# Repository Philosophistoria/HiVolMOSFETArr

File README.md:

View this project on [CADLAB.io](https://cadlab.io/project/1984). 

# HiVolMOSFETArr

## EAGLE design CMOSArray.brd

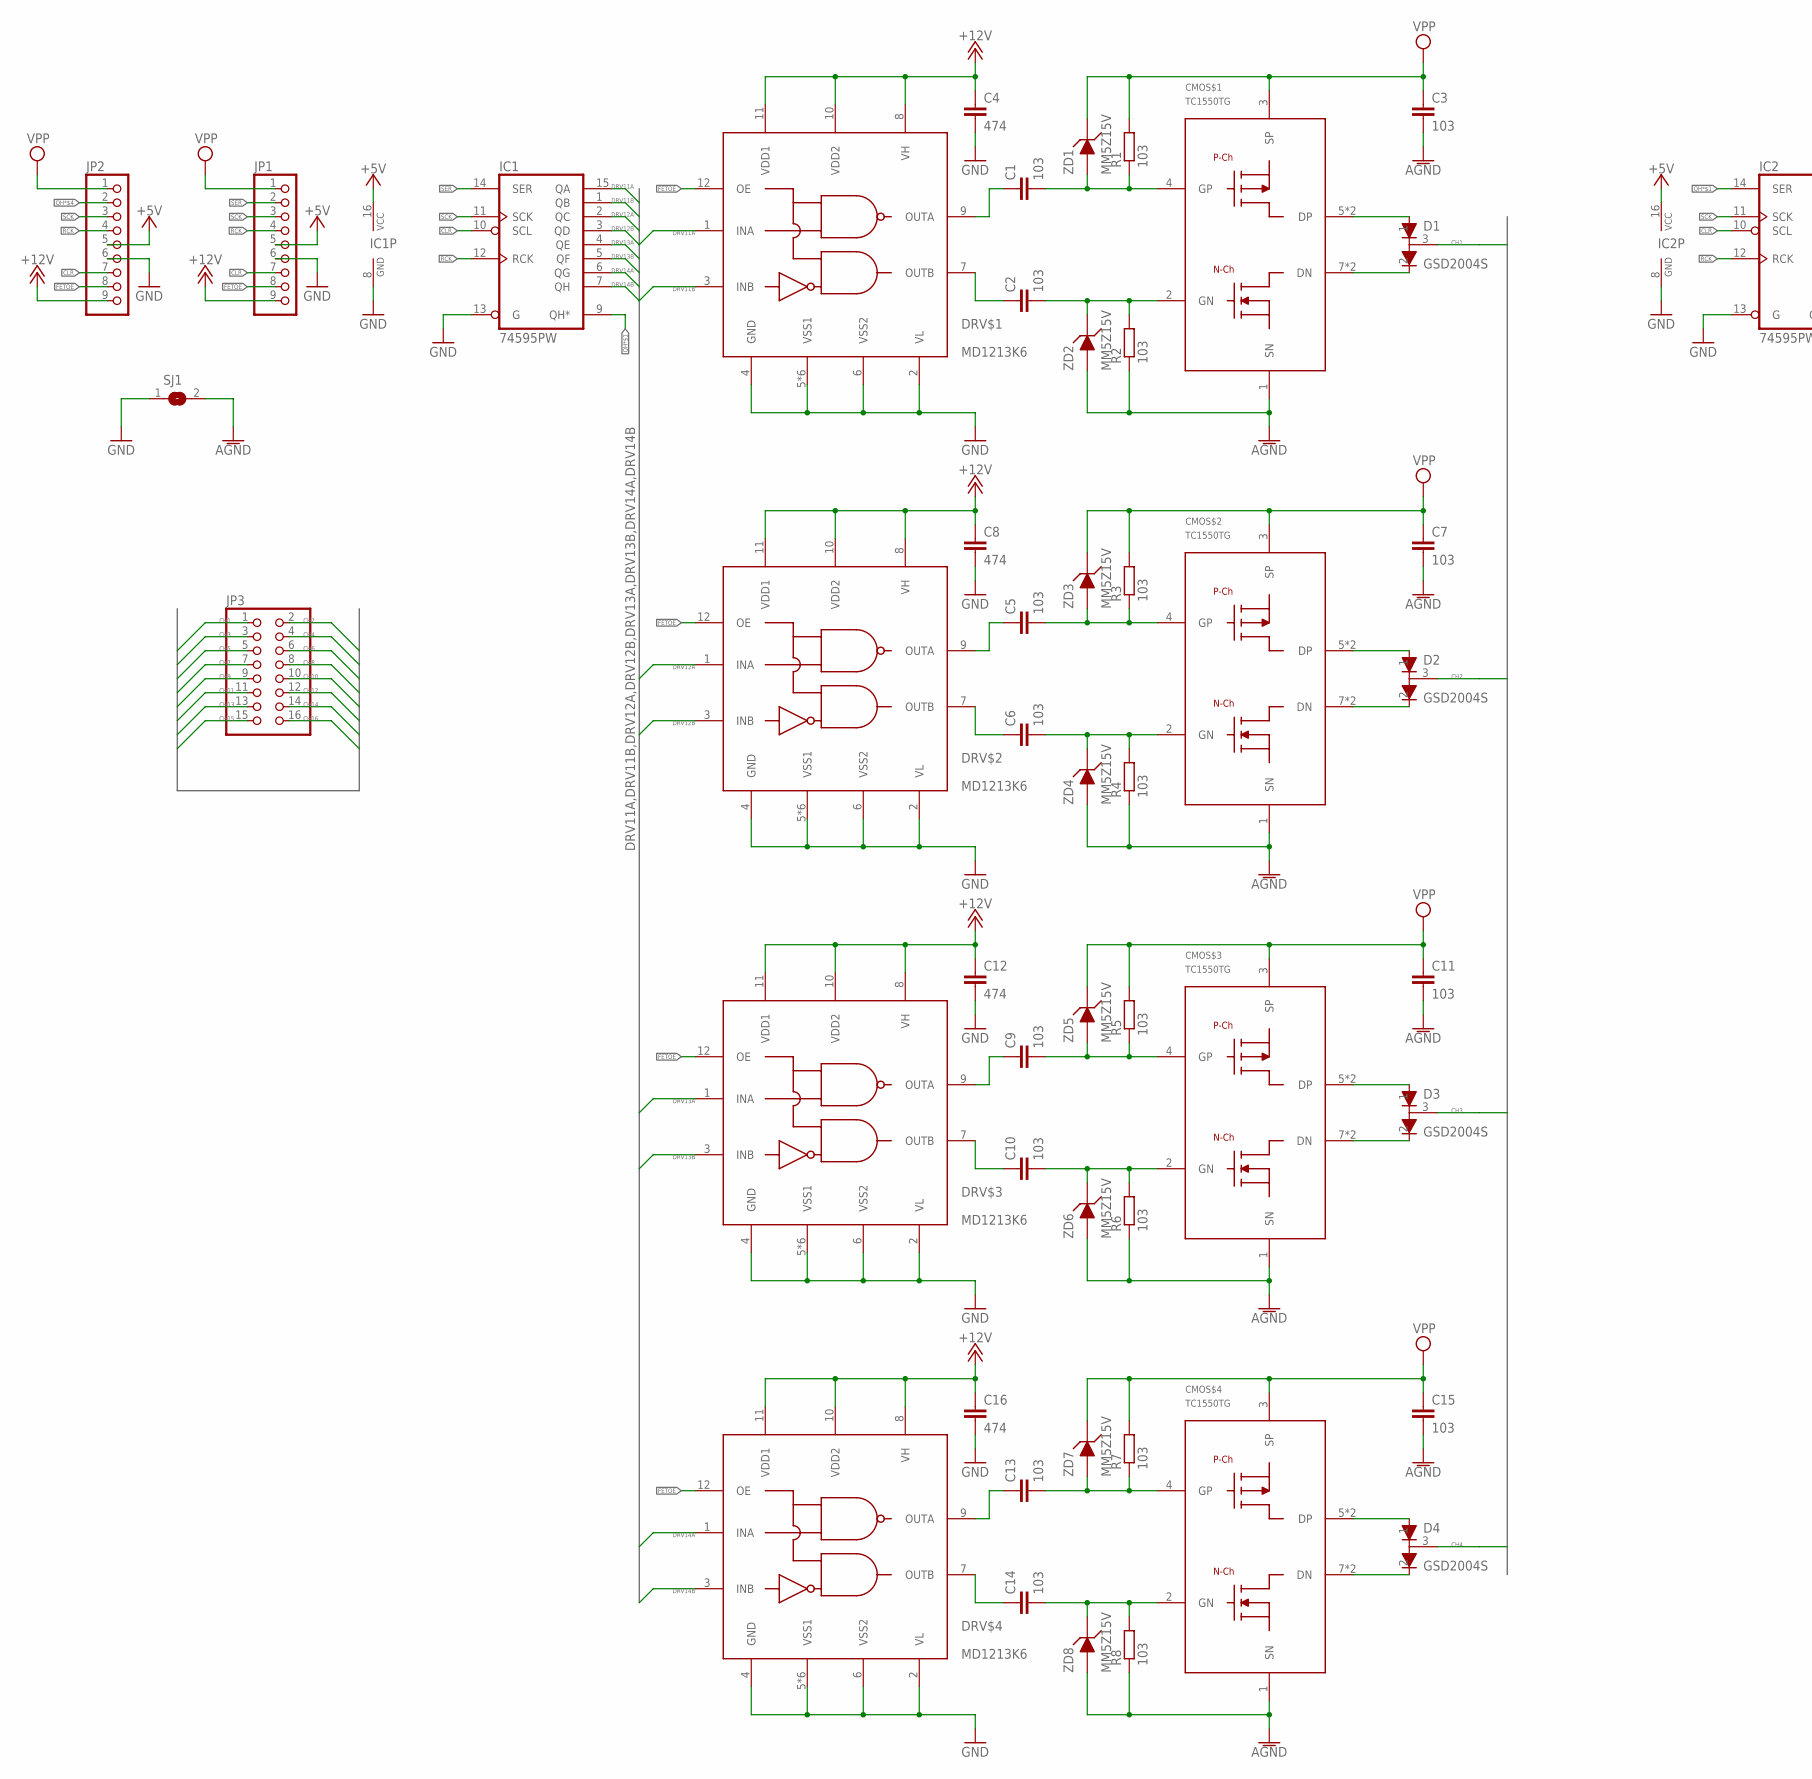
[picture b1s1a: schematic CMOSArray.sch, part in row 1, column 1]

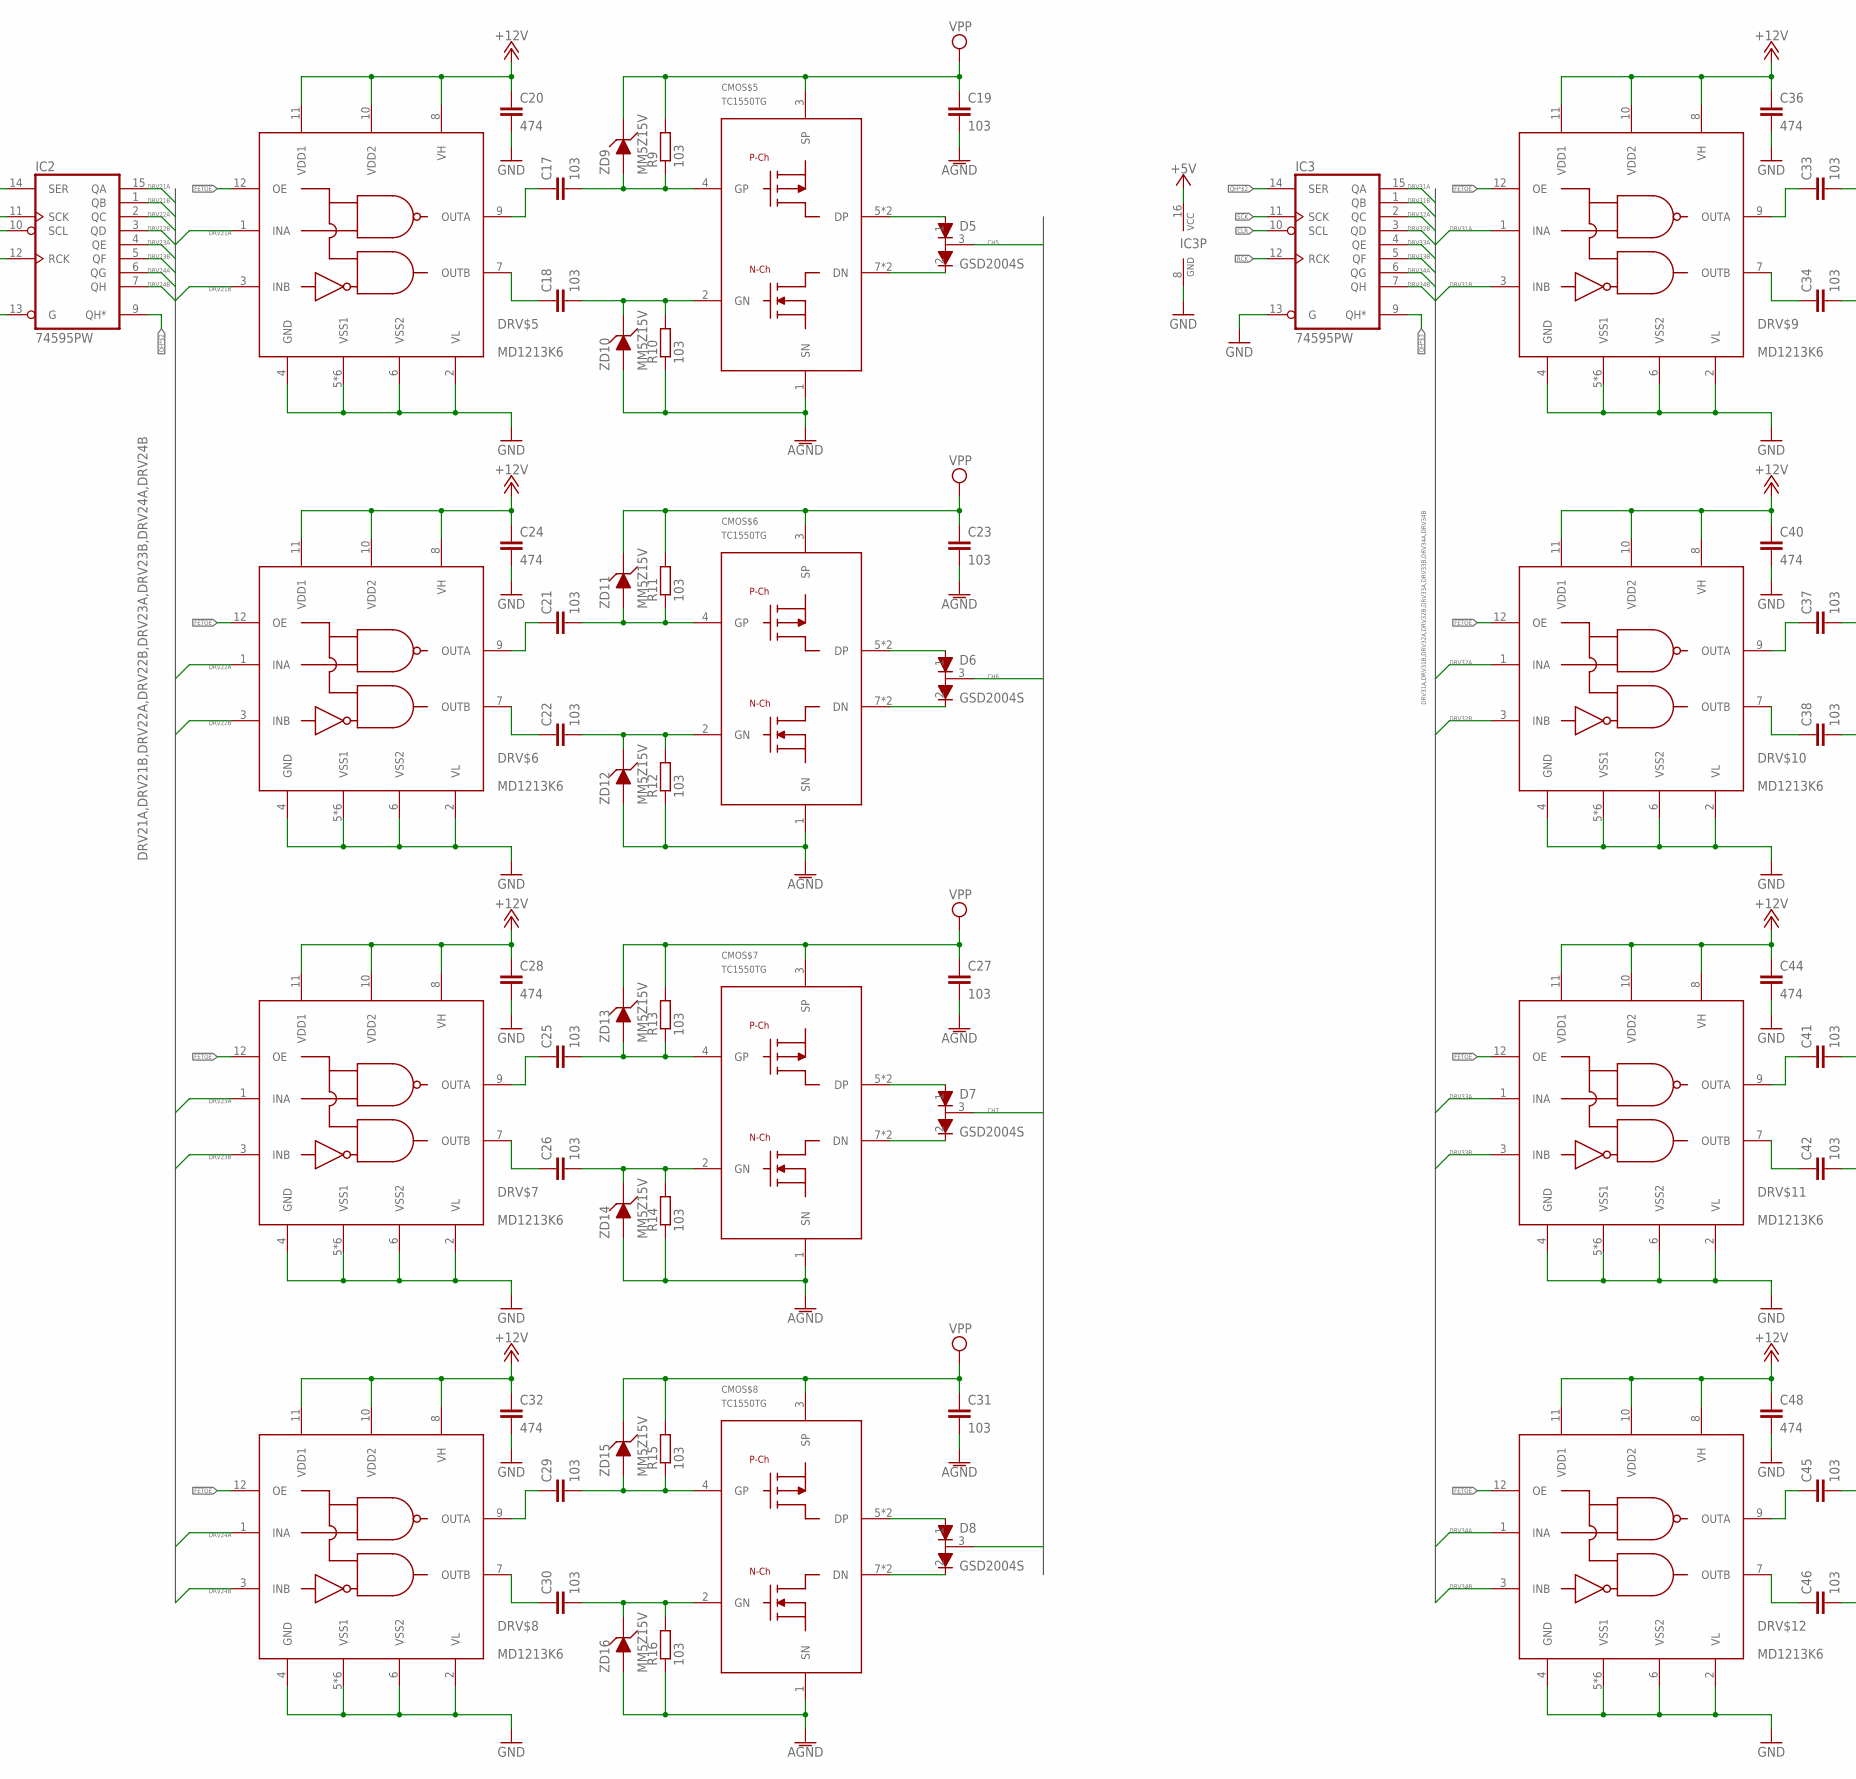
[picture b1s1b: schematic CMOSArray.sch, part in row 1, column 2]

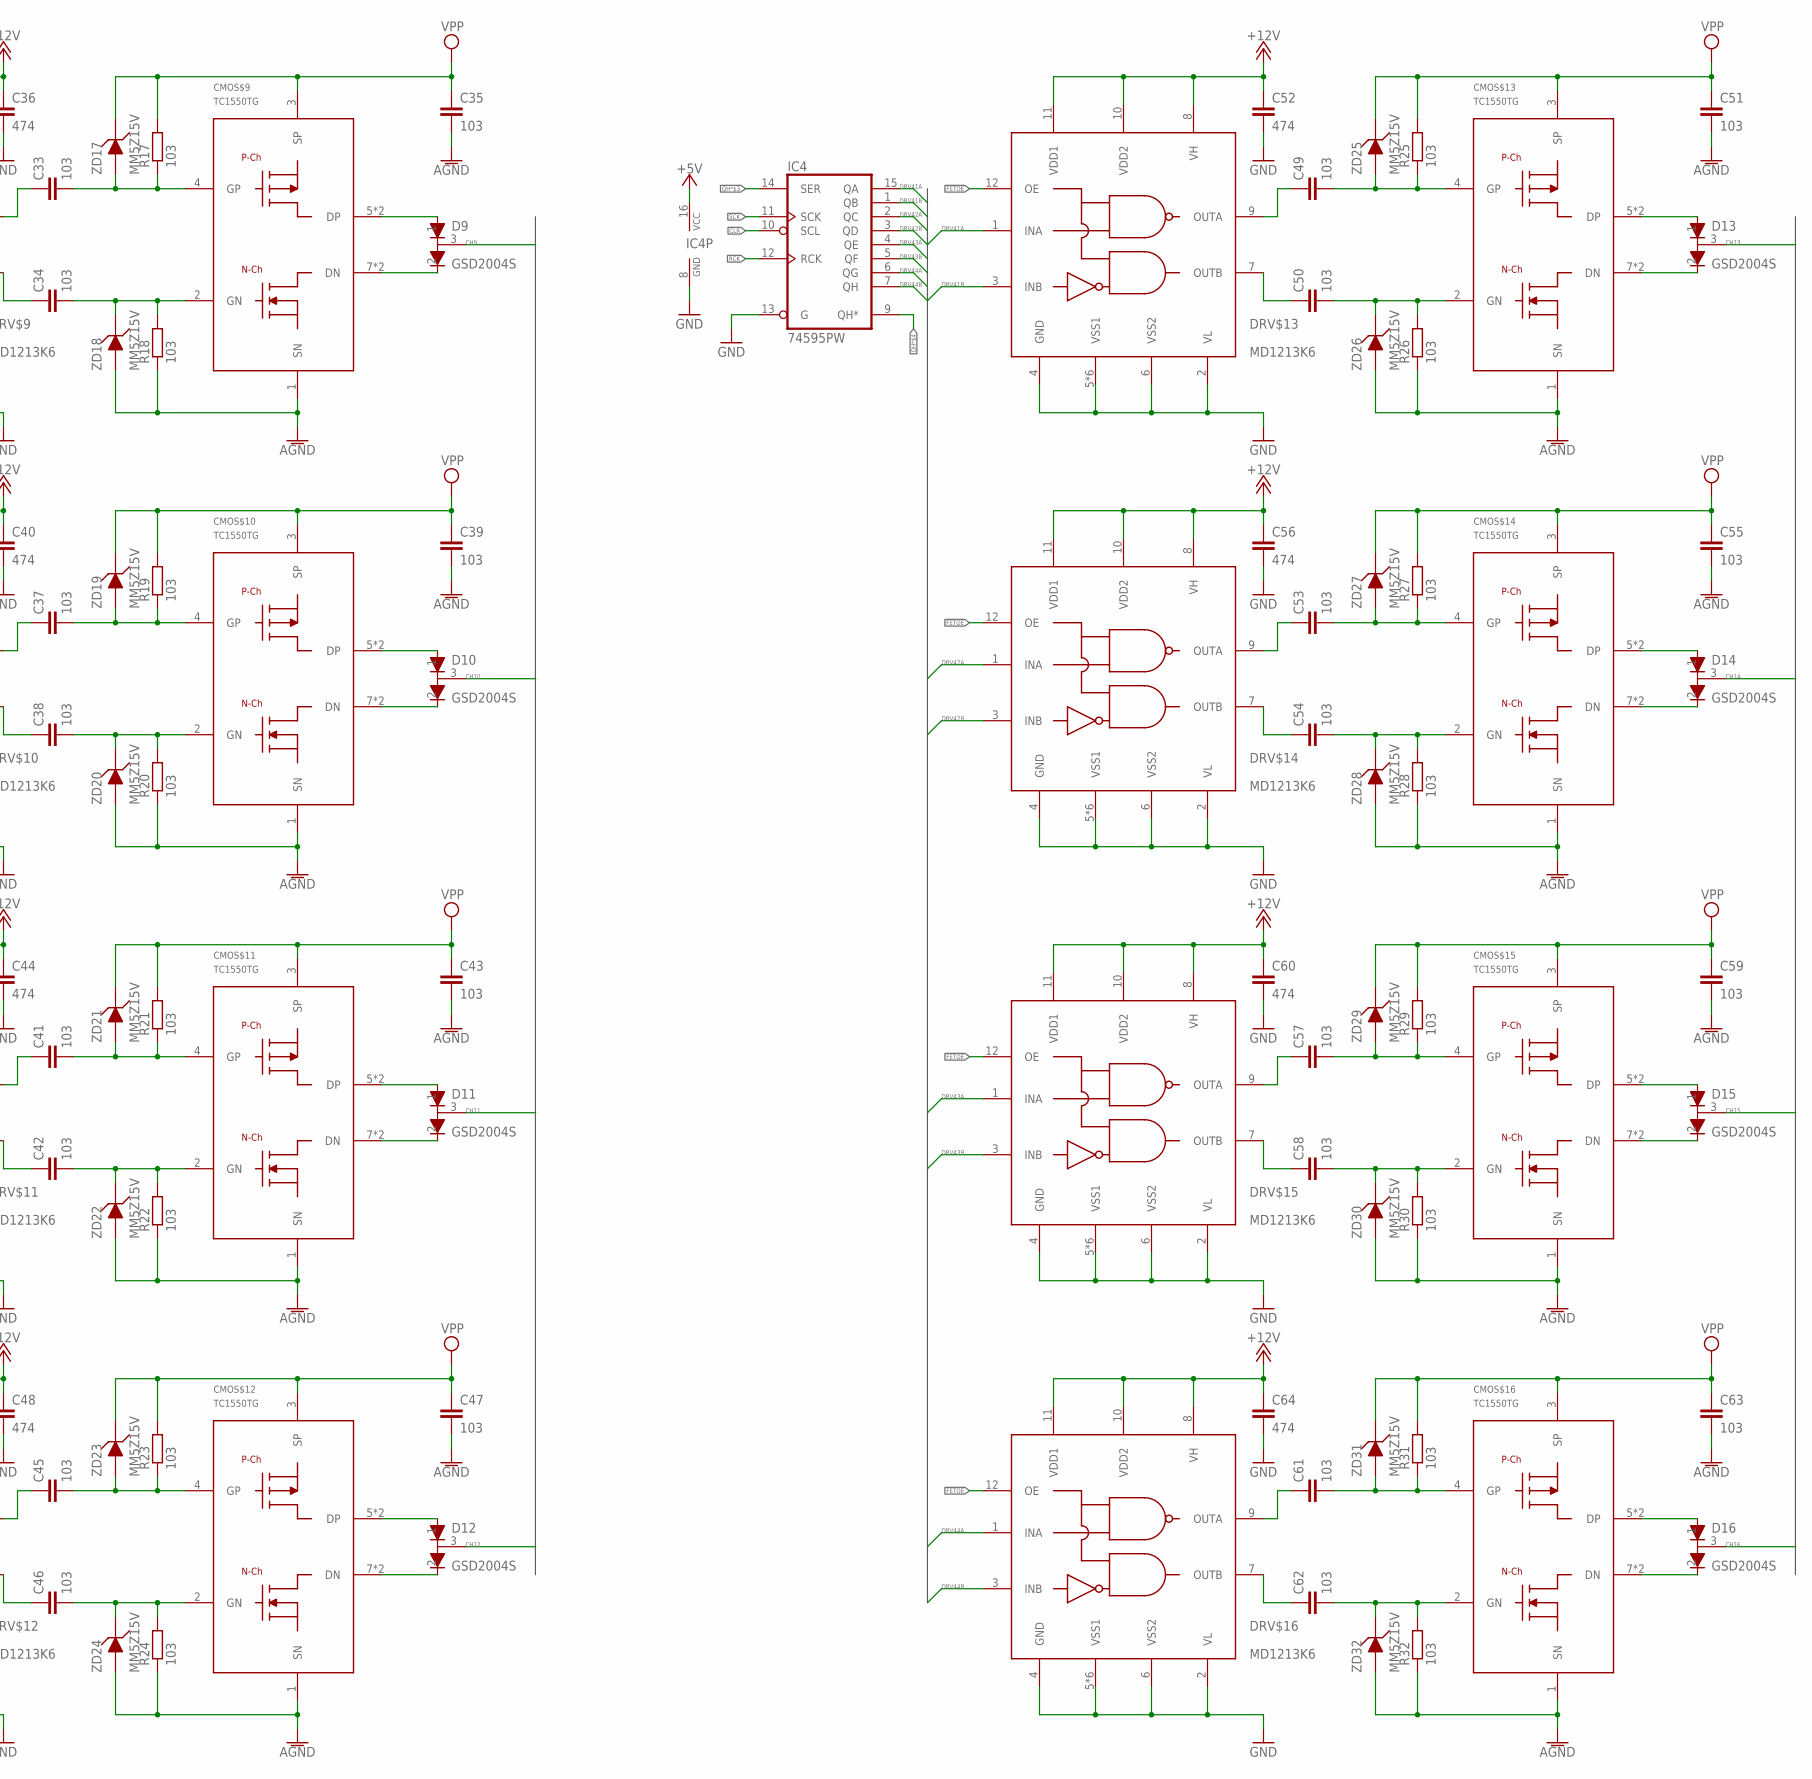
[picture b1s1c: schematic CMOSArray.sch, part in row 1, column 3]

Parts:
C1, C2, C3, C5, C6, C7, C9, C10, C11, C13, C14, C15, C17, C18, C19, C21, C22, C23, C25, C26, C27, C29, C30, C31, C33, C34, C35, C37, C38, C39, C41, C42, C43, C45, C46, C47, C49, C50, C51, C53, C54, C55, C57, C58, C59, C61, C62, C63: 103; C3216
C4, C8, C12, C16, C20, C24, C28, C32, C36, C40, C44, C48, C52, C56, C60, C64: 474; C0402
CMOS$1, CMOS$2, CMOS$3, CMOS$4, CMOS$5, CMOS$6, CMOS$7, CMOS$8, CMOS$9, CMOS$10, CMOS$11, CMOS$12, CMOS$13, CMOS$14, CMOS$15, CMOS$16: TC1550TG; SOIC-08LG
D1, D2, D3, D4, D5, D6, D7, D8, D9, D10, D11, D12, D13, D14, D15, D16: GSD2004S; SOT23
DRV$1, DRV$2, DRV$3, DRV$4, DRV$5, DRV$6, DRV$7, DRV$8, DRV$9, DRV$10, DRV$11, DRV$12, DRV$13, DRV$14, DRV$15, DRV$16: MD1213K6; QFN12
IC1, IC2, IC3, IC4: 74595PW; TTSOP16
JP1, JP2: PINHD-1X9; 1X09
JP3: PINHD-2X8; 2X08
R1, R2, R3, R4, R5, R6, R7, R8, R9, R10, R11, R12, R13, R14, R15, R16, R17, R18, R19, R20, R21, R22, R23, R24, R25, R26, R27, R28, R29, R30, R31, R32: 103; R0402
SJ1: SJ
ZD1, ZD2, ZD3, ZD4, ZD5, ZD6, ZD7, ZD8, ZD9, ZD10, ZD11, ZD12, ZD13, ZD14, ZD15, ZD16, ZD17, ZD18, ZD19, ZD20, ZD21, ZD22, ZD23, ZD24, ZD25, ZD26, ZD27, ZD28, ZD29, ZD30, ZD31, ZD32: MM5Z15V; SOD523

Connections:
+5V: IC1.16 (VCC), IC2.16 (VCC), IC3.16 (VCC), IC4.16 (VCC), JP1.5, JP2.5
+12V: C4.1, C8.1, C12.1, C16.1, C20.1, C24.1, C28.1, C32.1, C36.1, C40.1, C44.1, C48.1, C52.1, C56.1, C60.1, C64.1, DRV$1.8 (VH), DRV$1.10 (VDD2), DRV$1.11 (VDD1), DRV$2.8 (VH), DRV$2.10 (VDD2), DRV$2.11 (VDD1), DRV$3.8 (VH), DRV$3.10 (VDD2), DRV$3.11 (VDD1), DRV$4.8 (VH), DRV$4.10 (VDD2), DRV$4.11 (VDD1), DRV$5.8 (VH), DRV$5.10 (VDD2), DRV$5.11 (VDD1), DRV$6.8 (VH), DRV$6.10 (VDD2), DRV$6.11 (VDD1), DRV$7.8 (VH), DRV$7.10 (VDD2), DRV$7.11 (VDD1), DRV$8.8 (VH), DRV$8.10 (VDD2), DRV$8.11 (VDD1), DRV$9.8 (VH), DRV$9.10 (VDD2), DRV$9.11 (VDD1), DRV$10.8 (VH), DRV$10.10 (VDD2), DRV$10.11 (VDD1), DRV$11.8 (VH), DRV$11.10 (VDD2), DRV$11.11 (VDD1), DRV$12.8 (VH), DRV$12.10 (VDD2), DRV$12.11 (VDD1), DRV$13.8 (VH), DRV$13.10 (VDD2), DRV$13.11 (VDD1), DRV$14.8 (VH), DRV$14.10 (VDD2), DRV$14.11 (VDD1), DRV$15.8 (VH), DRV$15.10 (VDD2), DRV$15.11 (VDD1), DRV$16.8 (VH), DRV$16.10 (VDD2), DRV$16.11 (VDD1), JP1.9, JP2.9
AGND: C3.2, C7.2, C11.2, C15.2, C19.2, C23.2, C27.2, C31.2, C35.2, C39.2, C43.2, C47.2, C51.2, C55.2, C59.2, C63.2, CMOS$1.1 (SN), CMOS$2.1 (SN), CMOS$3.1 (SN), CMOS$4.1 (SN), CMOS$5.1 (SN), CMOS$6.1 (SN), CMOS$7.1 (SN), CMOS$8.1 (SN), CMOS$9.1 (SN), CMOS$10.1 (SN), CMOS$11.1 (SN), CMOS$12.1 (SN), CMOS$13.1 (SN), CMOS$14.1 (SN), CMOS$15.1 (SN), CMOS$16.1 (SN), R2.1, R4.1, R6.1, R8.1, R10.1, R12.1, R14.1, R16.1, R18.1, R20.1, R22.1, R24.1, R26.1, R28.1, R30.1, R32.1, SJ1.2, ZD2.P$2, ZD4.P$2, ZD6.P$2, ZD8.P$2, ZD10.P$2, ZD12.P$2, ZD14.P$2, ZD16.P$2, ZD18.P$2, ZD20.P$2, ZD22.P$2, ZD24.P$2, ZD26.P$2, ZD28.P$2, ZD30.P$2, ZD32.P$2
CH1: D1.3, JP3.1
CH2: D2.3, JP3.2
CH3: D3.3, JP3.3
CH4: D4.3, JP3.4
CH5: D5.3, JP3.5
CH6: D6.3, JP3.6
CH7: D7.3, JP3.7
CH8: D8.3, JP3.8
CH9: D9.3, JP3.9
CH10: D10.3, JP3.10
CH11: D11.3, JP3.11
CH12: D12.3, JP3.12
CH13: D13.3, JP3.13
CH14: D14.3, JP3.14
CH15: D15.3, JP3.15
CH16: D16.3, JP3.16
CLR: IC1.10 (SCL), IC2.10 (SCL), IC3.10 (SCL), IC4.10 (SCL), JP1.7, JP2.7
DRV11A: DRV$1.1 (INA), IC1.15 (QA)
DRV11B: DRV$1.3 (INB), IC1.1 (QB)
DRV12A: DRV$2.1 (INA), IC1.2 (QC)
DRV12B: DRV$2.3 (INB), IC1.3 (QD)
DRV13A: DRV$3.1 (INA), IC1.4 (QE)
DRV13B: DRV$3.3 (INB), IC1.5 (QF)
DRV14A: DRV$4.1 (INA), IC1.6 (QG)
DRV14B: DRV$4.3 (INB), IC1.7 (QH)
DRV21A: DRV$5.1 (INA), IC2.15 (QA)
DRV21B: DRV$5.3 (INB), IC2.1 (QB)
DRV22A: DRV$6.1 (INA), IC2.2 (QC)
DRV22B: DRV$6.3 (INB), IC2.3 (QD)
DRV23A: DRV$7.1 (INA), IC2.4 (QE)
DRV23B: DRV$7.3 (INB), IC2.5 (QF)
DRV24A: DRV$8.1 (INA), IC2.6 (QG)
DRV24B: DRV$8.3 (INB), IC2.7 (QH)
DRV31A: DRV$9.1 (INA), IC3.15 (QA)
DRV31B: DRV$9.3 (INB), IC3.1 (QB)
DRV32A: DRV$10.1 (INA), IC3.2 (QC)
DRV32B: DRV$10.3 (INB), IC3.3 (QD)
DRV33A: DRV$11.1 (INA), IC3.4 (QE)
DRV33B: DRV$11.3 (INB), IC3.5 (QF)
DRV34A: DRV$12.1 (INA), IC3.6 (QG)
DRV34B: DRV$12.3 (INB), IC3.7 (QH)
DRV41A: DRV$13.1 (INA), IC4.15 (QA)
DRV41B: DRV$13.3 (INB), IC4.1 (QB)
DRV42A: DRV$14.1 (INA), IC4.2 (QC)
DRV42B: DRV$14.3 (INB), IC4.3 (QD)
DRV43A: DRV$15.1 (INA), IC4.4 (QE)
DRV43B: DRV$15.3 (INB), IC4.5 (QF)
DRV44A: DRV$16.1 (INA), IC4.6 (QG)
DRV44B: DRV$16.3 (INB), IC4.7 (QH)
FETOE: DRV$1.12 (OE), DRV$2.12 (OE), DRV$3.12 (OE), DRV$4.12 (OE), DRV$5.12 (OE), DRV$6.12 (OE), DRV$7.12 (OE), DRV$8.12 (OE), DRV$9.12 (OE), DRV$10.12 (OE), DRV$11.12 (OE), DRV$12.12 (OE), DRV$13.12 (OE), DRV$14.12 (OE), DRV$15.12 (OE), DRV$16.12 (OE), JP1.8, JP2.8
GND: C4.2, C8.2, C12.2, C16.2, C20.2, C24.2, C28.2, C32.2, C36.2, C40.2, C44.2, C48.2, C52.2, C56.2, C60.2, C64.2, DRV$1.2 (VL), DRV$1.4 (GND), DRV$1.5 (VSS1), DRV$1.6 (VSS2), DRV$1.THP (VSS1), DRV$1.THV$1 (VSS1), DRV$1.THV$2 (VSS1), DRV$1.THV$3 (VSS1), DRV$1.THV$4 (VSS1), DRV$2.2 (VL), DRV$2.4 (GND), DRV$2.5 (VSS1), DRV$2.6 (VSS2), DRV$2.THP (VSS1), DRV$2.THV$1 (VSS1), DRV$2.THV$2 (VSS1), DRV$2.THV$3 (VSS1), DRV$2.THV$4 (VSS1), DRV$3.2 (VL), DRV$3.4 (GND), DRV$3.5 (VSS1), DRV$3.6 (VSS2), DRV$3.THP (VSS1), DRV$3.THV$1 (VSS1), DRV$3.THV$2 (VSS1), DRV$3.THV$3 (VSS1), DRV$3.THV$4 (VSS1), DRV$4.2 (VL), DRV$4.4 (GND), DRV$4.5 (VSS1), DRV$4.6 (VSS2), DRV$4.THP (VSS1), DRV$4.THV$1 (VSS1), DRV$4.THV$2 (VSS1), DRV$4.THV$3 (VSS1), DRV$4.THV$4 (VSS1), DRV$5.2 (VL), DRV$5.4 (GND), DRV$5.5 (VSS1), DRV$5.6 (VSS2), DRV$5.THP (VSS1), DRV$5.THV$1 (VSS1), DRV$5.THV$2 (VSS1), DRV$5.THV$3 (VSS1), DRV$5.THV$4 (VSS1), DRV$6.2 (VL), DRV$6.4 (GND), DRV$6.5 (VSS1), DRV$6.6 (VSS2), DRV$6.THP (VSS1), DRV$6.THV$1 (VSS1), DRV$6.THV$2 (VSS1), DRV$6.THV$3 (VSS1), DRV$6.THV$4 (VSS1), DRV$7.2 (VL), DRV$7.4 (GND), DRV$7.5 (VSS1), DRV$7.6 (VSS2), DRV$7.THP (VSS1), DRV$7.THV$1 (VSS1), DRV$7.THV$2 (VSS1), DRV$7.THV$3 (VSS1), DRV$7.THV$4 (VSS1), DRV$8.2 (VL), DRV$8.4 (GND), DRV$8.5 (VSS1), DRV$8.6 (VSS2), DRV$8.THP (VSS1), DRV$8.THV$1 (VSS1), DRV$8.THV$2 (VSS1), DRV$8.THV$3 (VSS1), DRV$8.THV$4 (VSS1), DRV$9.2 (VL), DRV$9.4 (GND), DRV$9.5 (VSS1), DRV$9.6 (VSS2), DRV$9.THP (VSS1), DRV$9.THV$1 (VSS1), DRV$9.THV$2 (VSS1), DRV$9.THV$3 (VSS1), DRV$9.THV$4 (VSS1), DRV$10.2 (VL), DRV$10.4 (GND), DRV$10.5 (VSS1), DRV$10.6 (VSS2), DRV$10.THP (VSS1), DRV$10.THV$1 (VSS1), DRV$10.THV$2 (VSS1), DRV$10.THV$3 (VSS1), DRV$10.THV$4 (VSS1), DRV$11.2 (VL), DRV$11.4 (GND), DRV$11.5 (VSS1), DRV$11.6 (VSS2), DRV$11.THP (VSS1), DRV$11.THV$1 (VSS1), DRV$11.THV$2 (VSS1), DRV$11.THV$3 (VSS1), DRV$11.THV$4 (VSS1), DRV$12.2 (VL), DRV$12.4 (GND), DRV$12.5 (VSS1), DRV$12.6 (VSS2), DRV$12.THP (VSS1), DRV$12.THV$1 (VSS1), DRV$12.THV$2 (VSS1), DRV$12.THV$3 (VSS1), DRV$12.THV$4 (VSS1), DRV$13.2 (VL), DRV$13.4 (GND), DRV$13.5 (VSS1), DRV$13.6 (VSS2), DRV$13.THP (VSS1), DRV$13.THV$1 (VSS1), DRV$13.THV$2 (VSS1), DRV$13.THV$3 (VSS1), DRV$13.THV$4 (VSS1), DRV$14.2 (VL), DRV$14.4 (GND), DRV$14.5 (VSS1), DRV$14.6 (VSS2), DRV$14.THP (VSS1), DRV$14.THV$1 (VSS1), DRV$14.THV$2 (VSS1), DRV$14.THV$3 (VSS1), DRV$14.THV$4 (VSS1), DRV$15.2 (VL), DRV$15.4 (GND), DRV$15.5 (VSS1), DRV$15.6 (VSS2), DRV$15.THP (VSS1), DRV$15.THV$1 (VSS1), DRV$15.THV$2 (VSS1), DRV$15.THV$3 (VSS1), DRV$15.THV$4 (VSS1), DRV$16.2 (VL), DRV$16.4 (GND), DRV$16.5 (VSS1), DRV$16.6 (VSS2), DRV$16.THP (VSS1), DRV$16.THV$1 (VSS1), DRV$16.THV$2 (VSS1), DRV$16.THV$3 (VSS1), DRV$16.THV$4 (VSS1), IC1.8 (GND), IC1.13 (G), IC2.8 (GND), IC2.13 (G), IC3.8 (GND), IC3.13 (G), IC4.8 (GND), IC4.13 (G), JP1.6, JP2.6, SJ1.1
unnamed: C1.1, DRV$1.9 (OUTA)
unnamed: C1.2, CMOS$1.4 (GP), R1.1, ZD1.P$2
unnamed: C2.1, DRV$1.7 (OUTB)
unnamed: C2.2, CMOS$1.2 (GN), R2.2, ZD2.P$1 (K)
unnamed: C5.1, DRV$2.9 (OUTA)
unnamed: CMOS$1.5 (DP), CMOS$1.6 (DP), D1.1
unnamed: CMOS$1.7 (DN), CMOS$1.8 (DN), D1.2
unnamed: C5.2, CMOS$2.4 (GP), R3.1, ZD3.P$2
unnamed: C6.1, DRV$2.7 (OUTB)
unnamed: C6.2, CMOS$2.2 (GN), R4.2, ZD4.P$1 (K)
unnamed: CMOS$2.5 (DP), CMOS$2.6 (DP), D2.1
unnamed: CMOS$2.7 (DN), CMOS$2.8 (DN), D2.2
unnamed: C9.1, DRV$3.9 (OUTA)
unnamed: C9.2, CMOS$3.4 (GP), R5.1, ZD5.P$2
unnamed: C10.1, DRV$3.7 (OUTB)
unnamed: C10.2, CMOS$3.2 (GN), R6.2, ZD6.P$1 (K)
unnamed: CMOS$3.5 (DP), CMOS$3.6 (DP), D3.1
unnamed: CMOS$3.7 (DN), CMOS$3.8 (DN), D3.2
unnamed: C13.1, DRV$4.9 (OUTA)
unnamed: C13.2, CMOS$4.4 (GP), R7.1, ZD7.P$2
unnamed: C14.1, DRV$4.7 (OUTB)
unnamed: C14.2, CMOS$4.2 (GN), R8.2, ZD8.P$1 (K)
unnamed: CMOS$4.5 (DP), CMOS$4.6 (DP), D4.1
unnamed: CMOS$4.7 (DN), CMOS$4.8 (DN), D4.2
unnamed: C17.1, DRV$5.9 (OUTA)
unnamed: C17.2, CMOS$5.4 (GP), R9.1, ZD9.P$2
unnamed: C18.1, DRV$5.7 (OUTB)
unnamed: C18.2, CMOS$5.2 (GN), R10.2, ZD10.P$1 (K)
unnamed: CMOS$5.5 (DP), CMOS$5.6 (DP), D5.1
unnamed: CMOS$5.7 (DN), CMOS$5.8 (DN), D5.2
unnamed: C21.1, DRV$6.9 (OUTA)
unnamed: C21.2, CMOS$6.4 (GP), R11.1, ZD11.P$2
unnamed: C22.1, DRV$6.7 (OUTB)
unnamed: C22.2, CMOS$6.2 (GN), R12.2, ZD12.P$1 (K)
unnamed: CMOS$6.5 (DP), CMOS$6.6 (DP), D6.1
unnamed: CMOS$6.7 (DN), CMOS$6.8 (DN), D6.2
unnamed: C25.1, DRV$7.9 (OUTA)
unnamed: C25.2, CMOS$7.4 (GP), R13.1, ZD13.P$2
unnamed: C26.1, DRV$7.7 (OUTB)
unnamed: C26.2, CMOS$7.2 (GN), R14.2, ZD14.P$1 (K)
unnamed: CMOS$7.5 (DP), CMOS$7.6 (DP), D7.1
unnamed: CMOS$7.7 (DN), CMOS$7.8 (DN), D7.2
unnamed: C29.1, DRV$8.9 (OUTA)
unnamed: C29.2, CMOS$8.4 (GP), R15.1, ZD15.P$2
unnamed: C30.1, DRV$8.7 (OUTB)
unnamed: C30.2, CMOS$8.2 (GN), R16.2, ZD16.P$1 (K)
unnamed: CMOS$8.5 (DP), CMOS$8.6 (DP), D8.1
unnamed: CMOS$8.7 (DN), CMOS$8.8 (DN), D8.2
unnamed: C33.1, DRV$9.9 (OUTA)
unnamed: C33.2, CMOS$9.4 (GP), R17.1, ZD17.P$2
unnamed: C34.1, DRV$9.7 (OUTB)
unnamed: C34.2, CMOS$9.2 (GN), R18.2, ZD18.P$1 (K)
unnamed: CMOS$9.5 (DP), CMOS$9.6 (DP), D9.1
unnamed: CMOS$9.7 (DN), CMOS$9.8 (DN), D9.2
unnamed: C37.1, DRV$10.9 (OUTA)
unnamed: C37.2, CMOS$10.4 (GP), R19.1, ZD19.P$2
unnamed: C38.1, DRV$10.7 (OUTB)
unnamed: C38.2, CMOS$10.2 (GN), R20.2, ZD20.P$1 (K)
unnamed: CMOS$10.5 (DP), CMOS$10.6 (DP), D10.1
unnamed: CMOS$10.7 (DN), CMOS$10.8 (DN), D10.2
unnamed: C41.1, DRV$11.9 (OUTA)
unnamed: C41.2, CMOS$11.4 (GP), R21.1, ZD21.P$2
unnamed: C42.1, DRV$11.7 (OUTB)
unnamed: C42.2, CMOS$11.2 (GN), R22.2, ZD22.P$1 (K)
unnamed: CMOS$11.5 (DP), CMOS$11.6 (DP), D11.1
unnamed: CMOS$11.7 (DN), CMOS$11.8 (DN), D11.2
unnamed: C45.1, DRV$12.9 (OUTA)
unnamed: C45.2, CMOS$12.4 (GP), R23.1, ZD23.P$2
unnamed: C46.1, DRV$12.7 (OUTB)
unnamed: C46.2, CMOS$12.2 (GN), R24.2, ZD24.P$1 (K)
unnamed: CMOS$12.5 (DP), CMOS$12.6 (DP), D12.1
unnamed: CMOS$12.7 (DN), CMOS$12.8 (DN), D12.2
unnamed: C49.1, DRV$13.9 (OUTA)
unnamed: C49.2, CMOS$13.4 (GP), R25.1, ZD25.P$2
unnamed: C50.1, DRV$13.7 (OUTB)
unnamed: C50.2, CMOS$13.2 (GN), R26.2, ZD26.P$1 (K)
unnamed: CMOS$13.5 (DP), CMOS$13.6 (DP), D13.1
unnamed: CMOS$13.7 (DN), CMOS$13.8 (DN), D13.2
unnamed: C53.1, DRV$14.9 (OUTA)
unnamed: C53.2, CMOS$14.4 (GP), R27.1, ZD27.P$2
unnamed: C54.1, DRV$14.7 (OUTB)
unnamed: C54.2, CMOS$14.2 (GN), R28.2, ZD28.P$1 (K)
unnamed: CMOS$14.5 (DP), CMOS$14.6 (DP), D14.1
unnamed: CMOS$14.7 (DN), CMOS$14.8 (DN), D14.2
unnamed: C57.1, DRV$15.9 (OUTA)
unnamed: C57.2, CMOS$15.4 (GP), R29.1, ZD29.P$2
unnamed: C58.1, DRV$15.7 (OUTB)
unnamed: C58.2, CMOS$15.2 (GN), R30.2, ZD30.P$1 (K)
unnamed: CMOS$15.5 (DP), CMOS$15.6 (DP), D15.1
unnamed: CMOS$15.7 (DN), CMOS$15.8 (DN), D15.2
unnamed: C61.1, DRV$16.9 (OUTA)
unnamed: C61.2, CMOS$16.4 (GP), R31.1, ZD31.P$2
unnamed: C62.1, DRV$16.7 (OUTB)
unnamed: C62.2, CMOS$16.2 (GN), R32.2, ZD32.P$1 (K)
unnamed: CMOS$16.5 (DP), CMOS$16.6 (DP), D16.1
unnamed: CMOS$16.7 (DN), CMOS$16.8 (DN), D16.2
QH*$1: IC1.9 (QH*), IC2.14 (SER)
QH*$2: IC2.9 (QH*), IC3.14 (SER)
QH*$3: IC3.9 (QH*), IC4.14 (SER)
QH*$4: IC4.9 (QH*), JP2.2
RCK: IC1.12 (RCK), IC2.12 (RCK), IC3.12 (RCK), IC4.12 (RCK), JP1.4, JP2.4
SCK: IC1.11 (SCK), IC2.11 (SCK), IC3.11 (SCK), IC4.11 (SCK), JP1.3, JP2.3
SER: IC1.14 (SER), JP1.2
VPP: C3.1, C7.1, C11.1, C15.1, C19.1, C23.1, C27.1, C31.1, C35.1, C39.1, C43.1, C47.1, C51.1, C55.1, C59.1, C63.1, CMOS$1.3 (SP), CMOS$2.3 (SP), CMOS$3.3 (SP), CMOS$4.3 (SP), CMOS$5.3 (SP), CMOS$6.3 (SP), CMOS$7.3 (SP), CMOS$8.3 (SP), CMOS$9.3 (SP), CMOS$10.3 (SP), CMOS$11.3 (SP), CMOS$12.3 (SP), CMOS$13.3 (SP), CMOS$14.3 (SP), CMOS$15.3 (SP), CMOS$16.3 (SP), JP1.1, JP2.1, R1.2, R3.2, R5.2, R7.2, R9.2, R11.2, R13.2, R15.2, R17.2, R19.2, R21.2, R23.2, R25.2, R27.2, R29.2, R31.2, ZD1.P$1 (K), ZD3.P$1 (K), ZD5.P$1 (K), ZD7.P$1 (K), ZD9.P$1 (K), ZD11.P$1 (K), ZD13.P$1 (K), ZD15.P$1 (K), ZD17.P$1 (K), ZD19.P$1 (K), ZD21.P$1 (K), ZD23.P$1 (K), ZD25.P$1 (K), ZD27.P$1 (K), ZD29.P$1 (K), ZD31.P$1 (K)

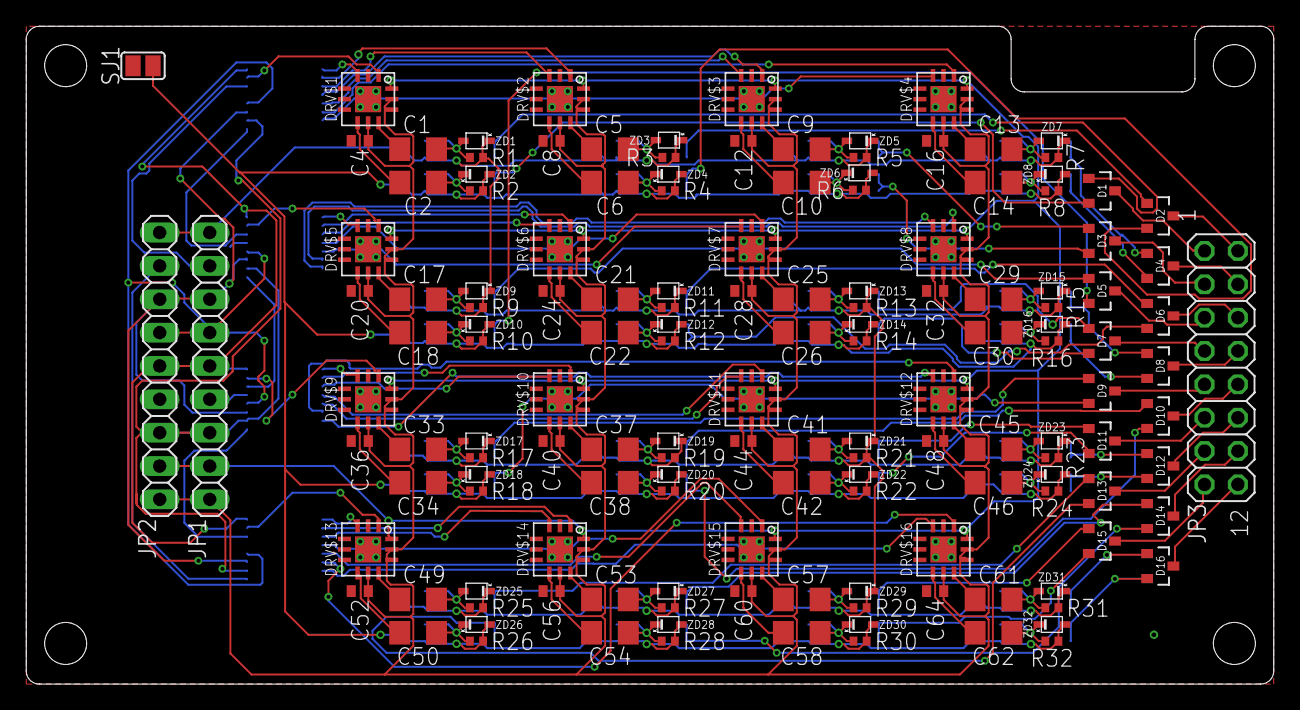
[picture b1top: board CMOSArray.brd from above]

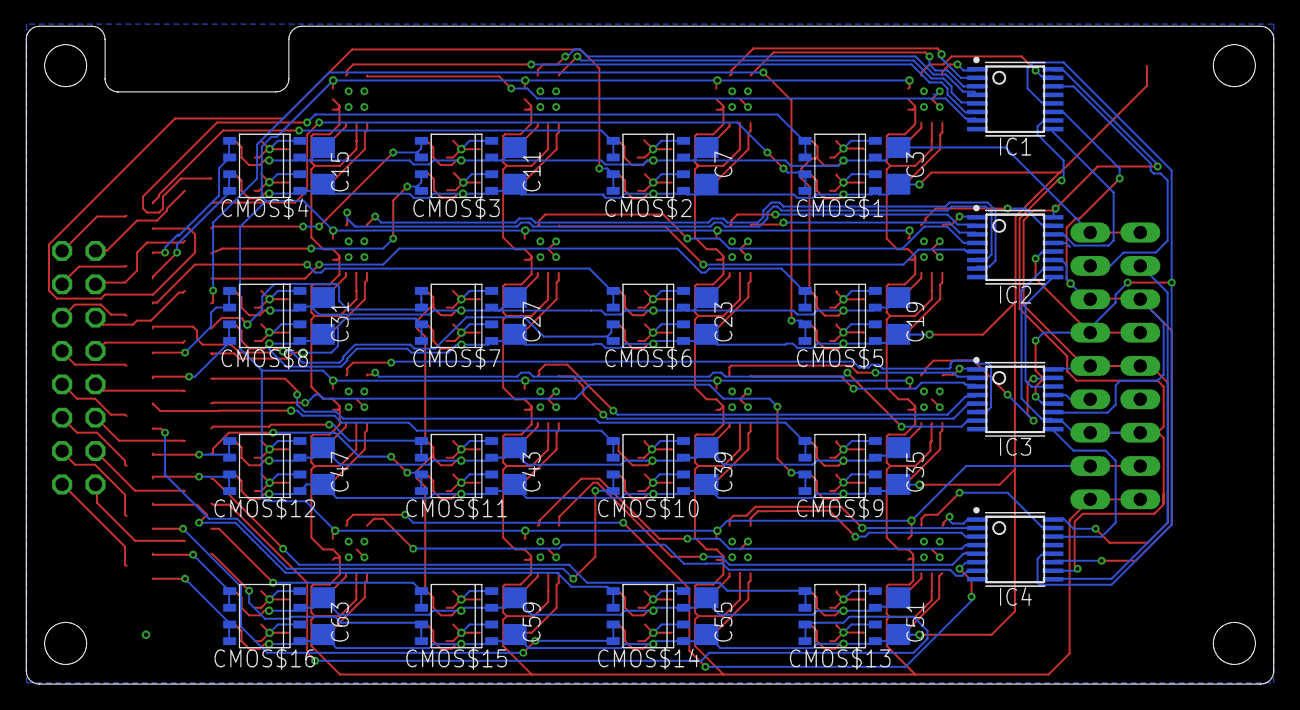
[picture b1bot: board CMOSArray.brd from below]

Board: 2 copper layers, 95.0 x 50.1 mm, 184 parts (36 on the bottom side), 158 nets.

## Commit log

2019-07-14 Previous implement that actually doesn't work because the typical app of md1213 and tc1550 was just for valtage power supply
2019-07-16 Backlink to CADLAB.io has been added.
